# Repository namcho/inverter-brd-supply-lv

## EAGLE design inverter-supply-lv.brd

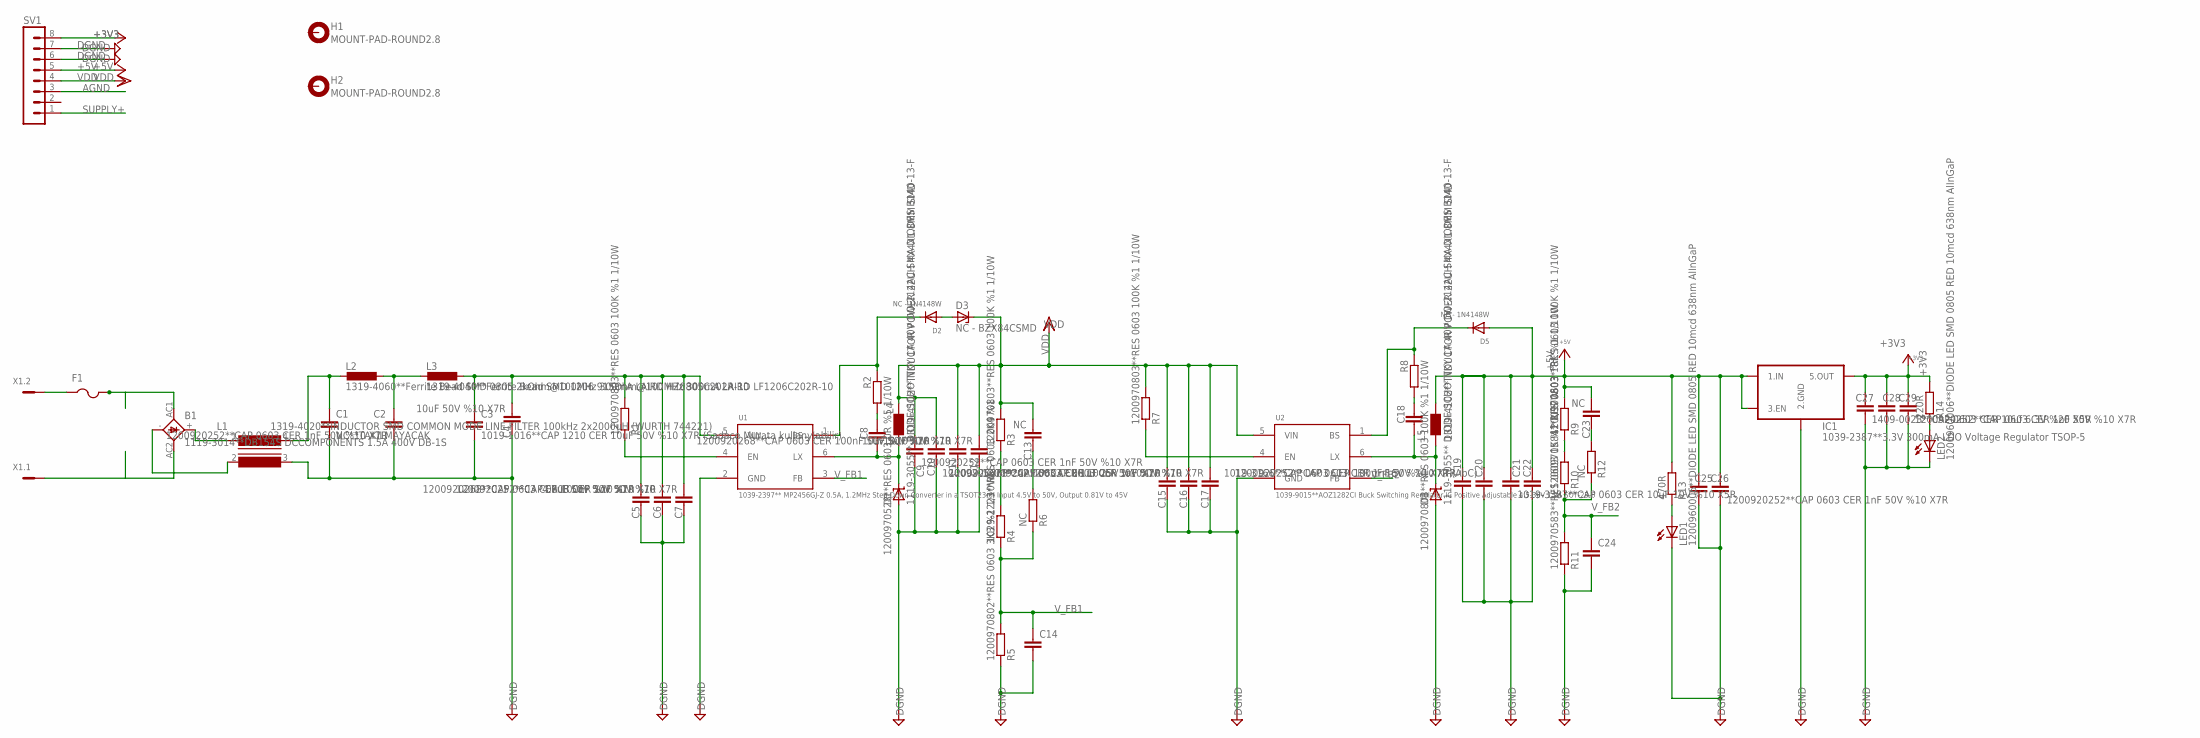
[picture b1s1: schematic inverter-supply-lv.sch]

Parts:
B1: 1119-3014**DB154S DCCOMPONENTS 1.5A 400V DB-1S; DF005S_DF10S
C1: NC**TAKILMAYACAK; C0603
C2, C7, C9, C17, C19, C26, C29: 1200920252**CAP 0603 CER 1nF 50V %10 X7R; C0603_ENKO
C3: 1019-1016**CAP 1210 CER 10uF 50V %10 X7R (Sadece 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; C1210
C4, C11, C12: 10uF 50V %10 X7R; C0805_ENKO
C5: 4.7uF 50V %10 X7R; C0805_ENKO
C6, C8, C10, C16, C18: 1200920268**CAP 0603 CER 100nF 50V %10 X7R; C0603_ENKO
C13, C23: NC; C0603_ENKO
C14, C24: 1200920271**CAP 0603 CER 10pF 50V%10 COG; C0603_ENKO
C15: 1200920567**CAP 0603 CER 1uF 25V %10X7R; C0603_ENKO
C20, C25, C28: 1019-3166**CAP 0603 CER 100nF 16V %10 X7R (AbC); C0603_ENKO
C21, C22: 1019-3387**CAP 0603 CER 10uF 10V %10 X5R; C0603_ENKO
C27: 1409-0023**CAP 0603 CER 10uf 6.3V %20 X5R; C0603_ENKO
D1, D4: 1119-3055** DIODE SCHOTTKY 1A 40V DO-214AC SMA DI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; SMA
D2, D5: NC - 1N4148W; SOD-123
D3: NC - BZX84CSMD; TO236
F1: PTCFUSE-1206; R1206
H1, H2: MOUNT-PAD-ROUND2.8; 2,8-PAD
IC1: 1039-2387**3.3V 300mA LDO Voltage Regulator TSOP-5; NCP115ASN330T2G
L1: 1319-4020**INDUCTOR SMD COMMON MODE LINE FILTER 1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; ARYA_COMMON_FILTER
L2: 1319-4060**Ferrite Bead SMD 0805 2kOhm@100MHz 300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; L2012C
L3: 1319-4040**Ferrite Bead SMD 1206 915Ohm@100MHz 30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; L3216C
L4, L5: 1319-4102**INDUCTOR POWER 22UH 4X4X1.8MM SMD; WE-PD2_S
LED1, LED2: 1200960006**DIODE LED SMD 0805 RED 10mcd 638nm Al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; CHIP-LED0805
R1, R3, R7, R8, R9: 1200970803**RES 0603 100K %1 1/10W; R0603_ENKO
R2: 1200970528**RES 0603 0R %5 1/10W; R0603_ENKO
R4: 1029-2223**RES 0603 2K4 %1; R0603_ENKO
R5: 1200970802**RES 0603 3K3 %1 1/10W; R0603_ENKO
R6, R12: NC; R0603_ENKO
R10: 1200970584**RES 0603 18K %1 1/10W; R0603_ENKO
R11: 1200970583**RES 0603 1K %1 1/10W; R0603_ENKO
R13: 470R; R0603_ENKO
R14: 220R; R0603_ENKO
SV1: MA08-1
U1: 1039-2397** MP2456GJ-Z 0.5A, 1.2MHz Step-Down Con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; AOZ1282CI-1
U2: 1039-9015**AOZ1282CI Buck Switching Regulator IC 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; AOZ1282CI-1
X1: 0289-9066**15EDGVC-3.81-02P-14; MCV2

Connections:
+3V3: C27.1, C28.1, C29.1, IC1.5 (5.OUT), R14.2, SV1.8
+5V: C19.2, C20.2, C21.1, C22.1, C23.2, C25.1, C26.1, D5.A, IC1.1 (1.IN), IC1.3 (3.EN), L5.1 (2), R9.2, R13.2, SV1.5
AGND: SV1.3
DGND: C1.1, C2.2, C3.1, C4.1, C5.1, C6.1, C7.1, C9.2, C10.1, C11.1, C12.1, C14.2, C15.1, C16.1, C17.1, C19.1, C20.1, C21.2, C22.2, C24.2, C25.2, C26.2, C27.2, C28.2, C29.2, D1.A, D4.A, IC1.2 (2.GND), L1.3, LED1.C, LED2.C, R5.1, R11.1, SV1.6, SV1.7, U1.2 (GND), U2.2 (GND)
unnamed: LED1.A, R13.1
unnamed: B1.AC1, F1.2
unnamed: C8.2, D1.C, L4.2 (1), U1.6 (LX)
unnamed: B1.-, L1.2
unnamed: C18.1, R8.2
unnamed: C8.1, R2.2
unnamed: C2.1, L2.2, L3.1
unnamed: F1.1, X1.2
unnamed: C18.2, D4.C, L5.2 (1), U2.6 (LX)
unnamed: D5.C, R8.1, U2.1 (BS)
unnamed: C3.2, C4.2, C5.2, C6.2, C7.2, L3.2, R1.2, U1.5 (VIN)
unnamed: B1.AC2, X1.1
unnamed: C1.2, L1.4, L2.1
unnamed: R7.1, U2.4 (EN)
unnamed: LED2.A, R14.1
unnamed: B1.+, L1.1
unnamed: R1.1, U1.4 (EN)
unnamed: R3.1, R4.2
unnamed: D2.C, R2.1, U1.1 (BS)
unnamed: C13.1, R6.2
unnamed: D2.A, D3.A
unnamed: R9.1, R10.2
unnamed: C23.1, R12.2
SUPPLY+: SV1.1
VDD: C9.1, C10.2, C11.2, C12.2, C13.2, C15.2, C16.2, C17.2, D3.C, L4.1 (2), R3.2, R7.2, SV1.4, U2.5 (VIN)
V_FB1: C14.1, R4.1, R5.2, R6.1, U1.3 (FB)
V_FB2: C24.1, R10.1, R11.2, R12.1, U2.3 (FB)

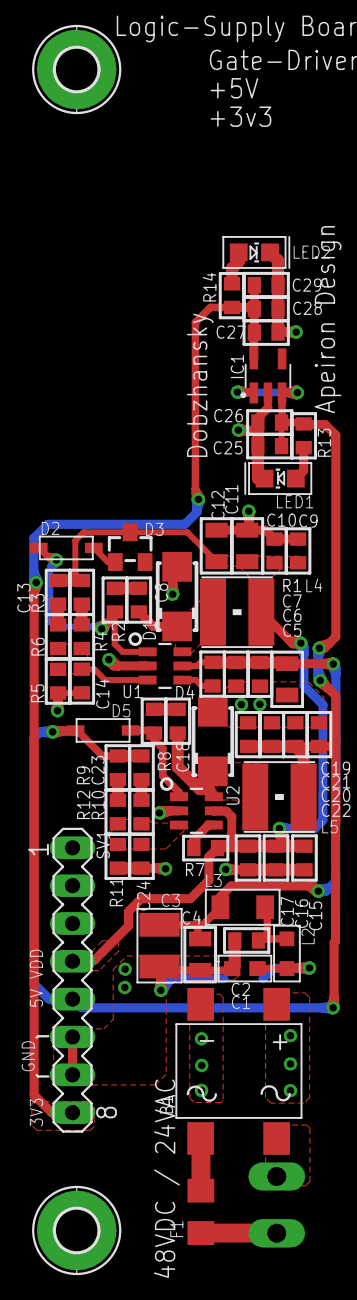
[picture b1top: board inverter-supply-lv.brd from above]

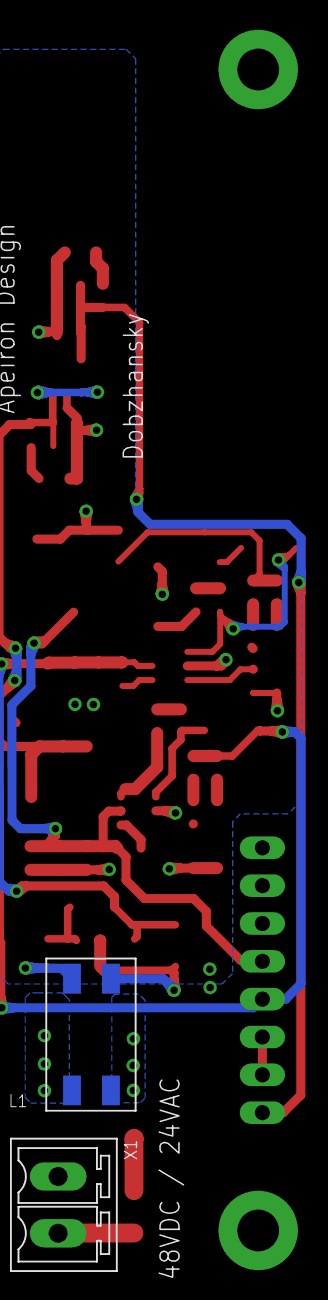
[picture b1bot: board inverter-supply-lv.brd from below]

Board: 3 copper layers, 64 parts (2 on the bottom side), 29 nets.

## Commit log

2021-06-14 ignore dosyasi olusturuldu.
2021-06-14 Dusuk giris voltajli besleme karti semasi cizildi.
2021-06-14 Girise fuse eklendi.
2021-06-14 Yerleşim yapıldı
2021-06-16 Bitti
2021-06-16 Tutturma pad'leri eklendi, soketler icin aciklayici text'ler eklendi.
2021-06-16 Board uzerine aciklayici bilgiler eklendi.
2021-06-16 Kart'dan karta baglanti pad'leri yerlestirildi.
2021-06-16 Kart vidalama pad pozisyonlari ayarlandi ve Apeiron Design reklami yapildi.
2021-06-16 Ana kart 8'li baglanti soket koordinati ayarlandi.
2021-06-17 Dobzhansky onurlandiralim.
2021-06-29 Malzeme degerlerinde degisiklikler yapilmisti sanirim.

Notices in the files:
parts and their libraries:
wuerth-elektronik: Copyright: Würth Elektronik eiSos
